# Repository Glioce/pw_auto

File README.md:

# pw_auto
PowherWheels modificado que se estaciona automáticamente.  

El cerebro del vehículo es una TIVA C EK-TM4C1294XL  
https://www.ti.com/tool/EK-TM4C1294XL  

> Tiva C Series  
> Connected LaunchPad  
> Booster Pack 2  
> TM4C1294  
> EK - TM4C1294XL  
> ARM Cortex M4F-Based  

## Ambientes de desarrollo
Se puede programar con las herramientas que proporciona Texas Instruments o con Energia IDE  
CCS IDE https://www.ti.com/tool/CCSTUDIO  
TivaWare https://www.ti.com/tool/SW-TM4C  
¿Editor online? https://dev.ti.com/  

Energia IDE se puede descargar sin registrarse y es como Arduino  
https://energia.nu/  
Tarjetas soportadas  
https://energia.nu/pinmaps/  

### Usando Energia
Descargar y abrir el IDE Energia. Instalar el paquete para programar Tiva C
en el menú Herramientas / Placas / Gestor de tarjetas, buscar TM, instalar.  

Conectar la tarjeta a la computadora usando el conector debug.
(parece que el otro conector es USB OTG)  

Guide to the TM4C129 Connected LaunchPad (EK-TM4C1294XL)  
https://energia.nu/pinmaps/ek-tm4c1294xl/  

Language reference (se parece a Arduino)  
https://energia.nu/reference/  

### Usando Code Composer Studio (CCS)
Iniciar el instalador y seleccionar el tipo de procesador de la tarjeta para instalar definiciones y compiladores.  

---

### Algoritmo
El vehículo se puede controlar de forma manual o funcionar en modo automático.
Cuando está en modo automático usa 4 sensores ultrasónicos. Dos sensores están instalados en el costado izquierdo del vehículo,
un sensor está instalado en la parte frontal y otro en la parte trasera.

Estado 0  
El vehículo avanza en línea recta. Hasta que los dos sensores laterales encuentran espacio suficiente para estacionarse.  
¿Necesita condiciones especiales para evitar errores?  
Los sensores pueden detectar suficiente espacio desde el inicio.  
Los sensores pueden detectar obstáculos desde el inicio (condición ideal).  
Un sensor detecta obstáculo y el otro ve un espacio libre. ¿Debe avanzar hacia adelante siempre?  
Al avanzar desde la condición ideal detectando obstáculos con los dos sensores laterales, ¿debe detectarse espacio con el sensor frontal primero?  
Lo más fácil es avanzar hasta que los dos sensores laterales detectan espacio.  

Estado 1  
Cuando los sensores laterales detectaron espacio. El vehículo sigue avanzando hasta que el sensor lateral frontal detecta obstáculo.  
Es importante notar que en los estados no se usan temporizadores,
solo se leen valores de los sensores para actuar. De esa forma la velocidad de desplazamiento se puede ajustar sin modificiar otras partes del programa.  

Estado 2  
La dirección gira a la izquierda y el vehículo comienza a avanzar en reversa.
El vehículo se introduce en el espacio disponible hasta que el sensor trasero detecta obstáculo.  
La distancia de detección de obstáculo debe ser un poco mayor a la distancia de estados anteriores.  

Estado 3  
La dirección gira a la derecha y el vehículo sigue avanzando en reversa.  
Con este movimiento el vehículo se va alineando al rectángulo disponible para estacionarse.  
Se detiene cuando detecta de nuevo un obstáculo con el sensor trasero.  

Estado 4  
Reposo. El vehículo ya está estacionado. En teoría debería quedar alineado y los sensores laterales deberían detectar un obstáculo cercano.  
Tal vez se puede mover un poco para que los sensores frontal y trasero detecten la misma distancia a sus respectivos obstáculos.  

Prevención de colisiones.  
Cada estado usa las lecturas de sensores específicos para determinar si debe cambiar al siguiente estado,
sin embargo, se usan los 4 sensores todo el tiempo. Si se detecta un objeto cercano en un momento inesperado, el vehículo se detiene.  

----
¿Ejemplo BLE?  
https://www.ti.com/tool/TIDM-TM4C129XBLE  

----
## Notas

Torque de wiper motor  
https://www.youtube.com/watch?v=hoxBkrD4xCo  

Ideas para wiper motor  
http://www.scary-terry.com/wipmtr/wipmtr2.htm  

L298 datasheet  
https://www.sparkfun.com/datasheets/Robotics/L298_H_Bridge.pdf  

IBT_2 tienada invento  
https://web.inventoteca.com/shop/product/puente-h-ibt-2-arduino-278?search=ibt  
http://www.hessmer.org/blog/2013/12/28/ibt-2-h-bridge-with-arduino/  

BTS7960  
https://www.handsontec.com/dataspecs/module/BTS7960%20Motor%20Driver.pdf  
https://articulo.mercadolibre.com.mx/MLM-613082284-modulo-puente-h-bts7960-43a-arduino-pic-_JM  

Puente H TIP41  
https://articulo.mercadolibre.com.mx/MLM-559425400-puente-h-4-amps-3-36-v-arduino-pic-robot-_JM  
https://www.youtube.com/watch?v=dnmWR5z8qPU  

Teoría Puente H con transistores de potencia  
http://tecnobotica.com/index.php/diplomados/tutoriales/41-puente-h-con-transistores  
https://www.diarioelectronicohoy.com/blog/el-puente-h-h-bridge  
http://salvador.maciashernandez.com/Proyectos/PuenteH/PuenteH.htm  
https://www.neoteo.com/puente-h-con-mosfet-para-motores-cc/  

Servos  
https://servodatabase.com/servo/towerpro/mg995  
https://servodatabase.com/servo/futaba/s3004  

### Varios videos

Ejemplo de carrito modificado. No tiene mucha info de la parte mecánica, pero explica el tipo de motores utilizados y las conexiones  
https://www.youtube.com/watch?v=AcVkwMPjTos  

https://www.youtube.com/watch?v=kzbhZqHqDM4  
También recomienda actuador lineal para la dirección  

https://www.youtube.com/watch?v=bRXtnwlUMdg  
Mejor detalle del actuador lineal  

https://www.youtube.com/watch?v=jNAeYGaALlQ  
Versión con servo. El carro es pequeño  

https://www.youtube.com/watch?v=kbLrQpJD--s  
Polea, alambre y motorreductor de la ventana de un Chevy Cavalier  
No menciona el sensor que utiliza para saber la posición del motor  
https://imgur.com/a/JXyOk  
Diagrama  

https://www.youtube.com/watch?v=n1nEr1FM19E  
Usar circuito de servo para controlar otro motorreductor  

https://www.youtube.com/watch?v=bURsvNdro4o  
Convertir motor de limpia parabrisas a servo  

https://www.youtube.com/watch?v=bi74u1eqCec  
Usa motor de regulador de ventana  

https://www.youtube.com/watch?v=spRwU4s4rTw  
Motor de limpia parabrisas convertido a servo  

https://www.youtube.com/watch?v=T5xMn2v7UGc  
Otra conversión de motor de limpia parabrisas a servo

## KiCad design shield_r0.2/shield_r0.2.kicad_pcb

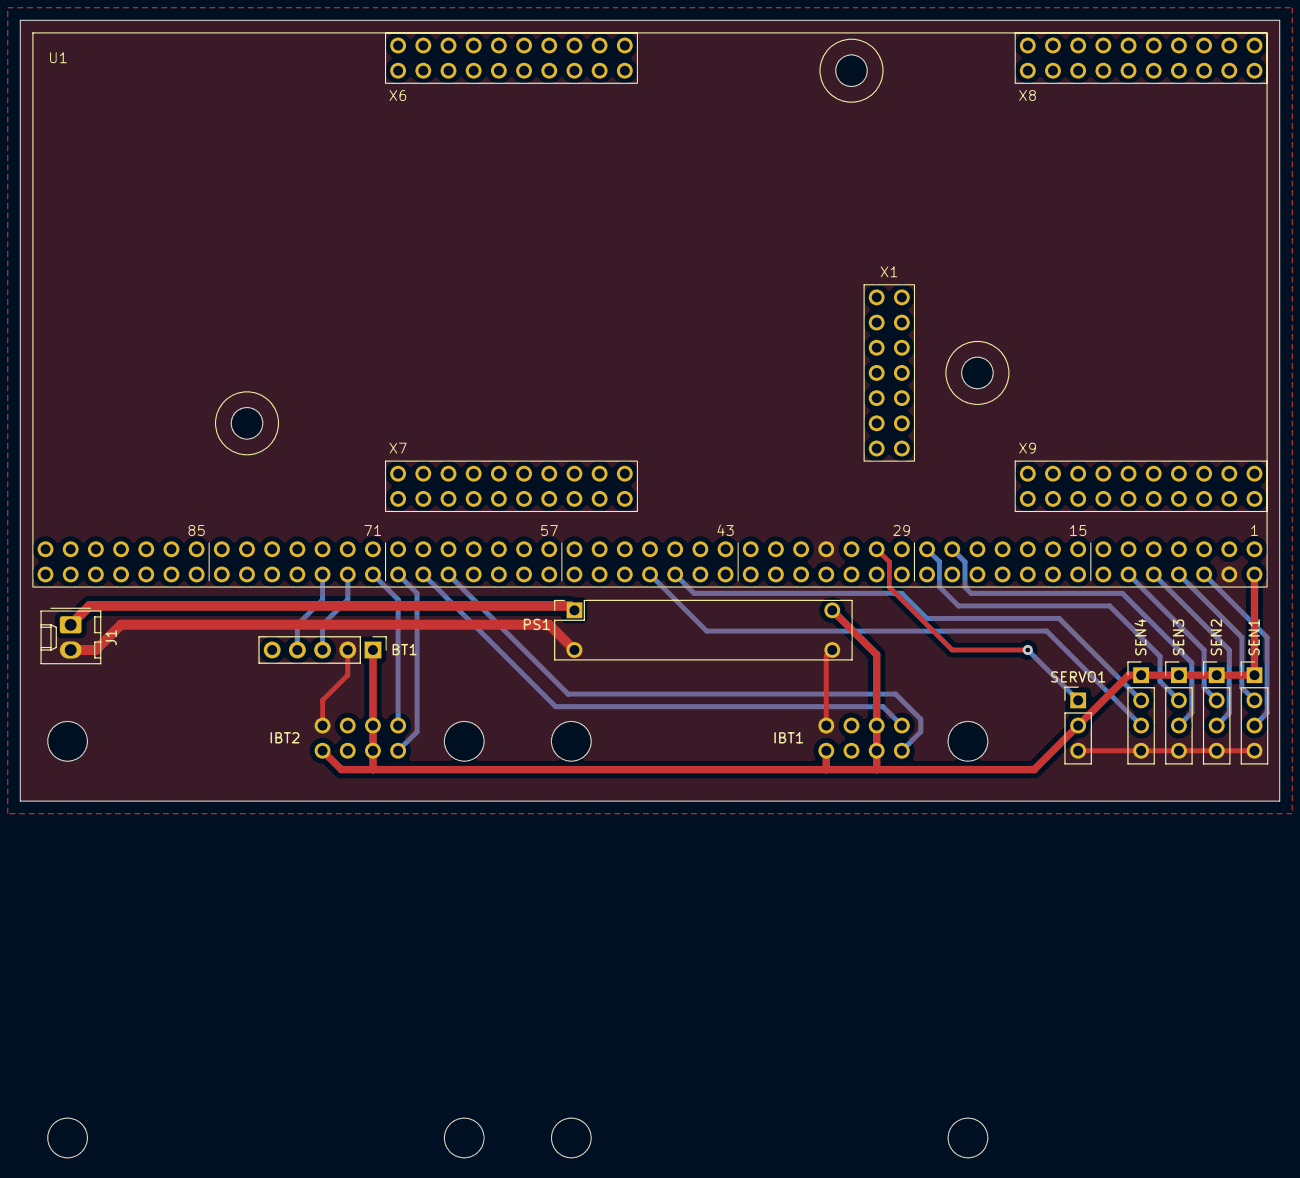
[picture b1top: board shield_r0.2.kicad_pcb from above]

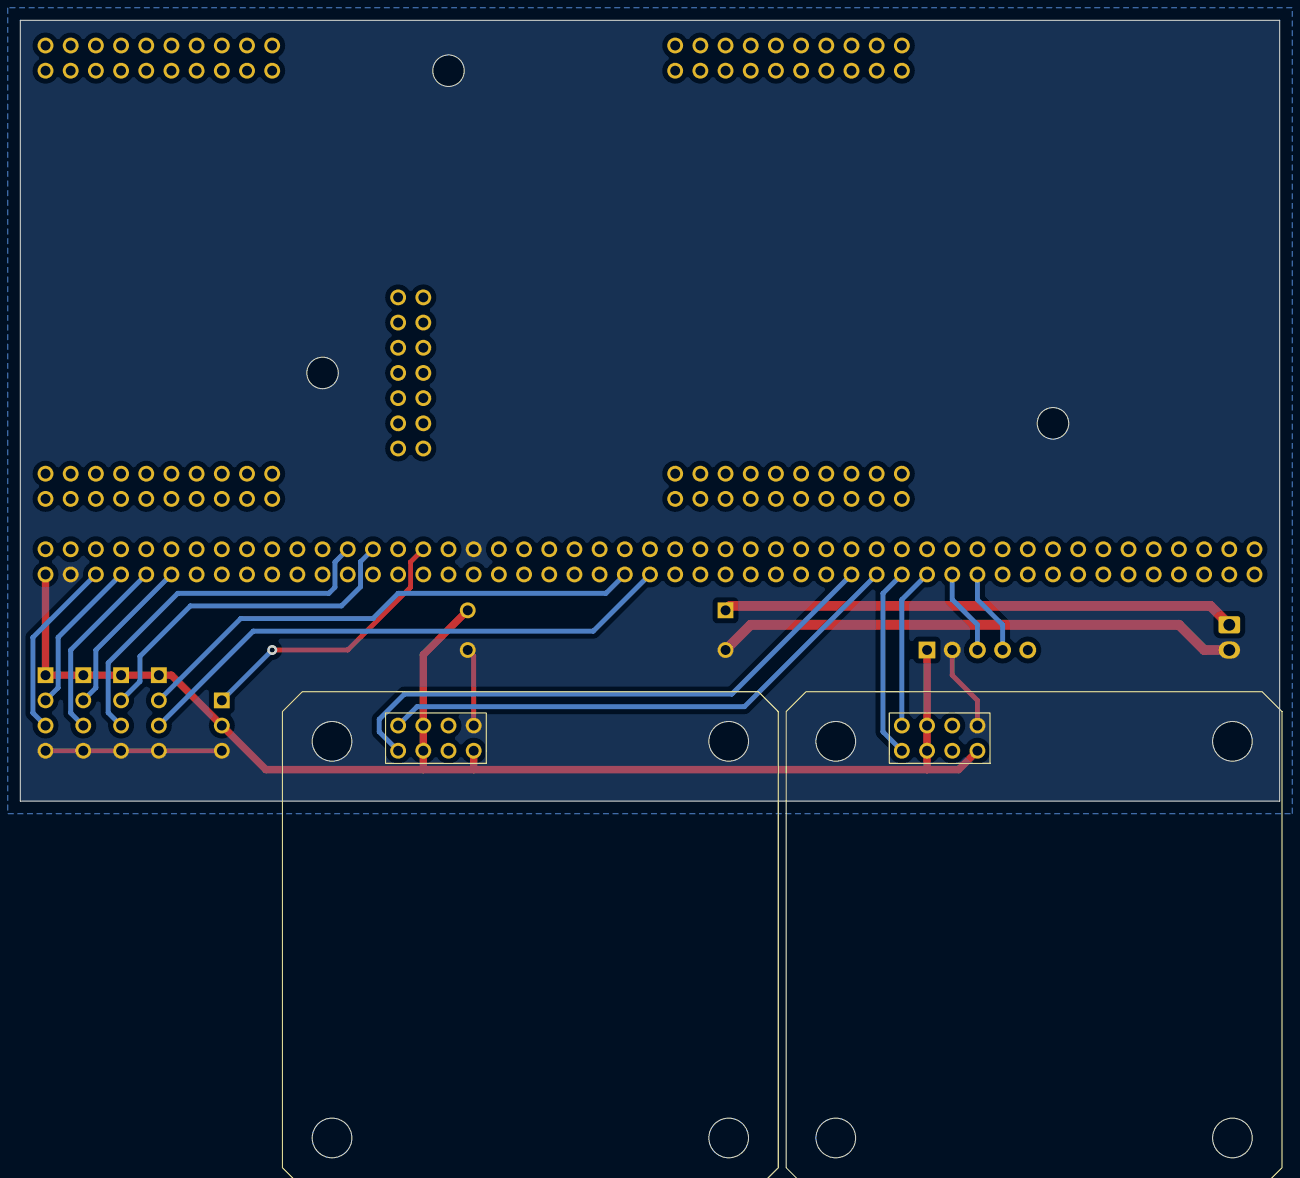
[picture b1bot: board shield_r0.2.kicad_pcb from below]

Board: 2 copper layers, 127.0 x 78.7 mm, 11 parts (2 on the bottom side), 18 nets.

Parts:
BT1: Conn_01x05; PinHeader_1x05_P2.54mm_Vertical
IBT1, IBT2: Conn_02x04_Odd_Even; IBT_2-01
J1: 12V; Molex_KK-254_AE-6410-02A_1x02_P2.54mm_Vertical
PS1: REGULADOR; PinHeader_2x02_P2.54mm_Vertical
SEN1, SEN2, SEN3, SEN4: Conn_01x04; PinHeader_1x04_P2.54mm_Vertical
SERVO1: Conn_01x03; PinHeader_1x03_P2.54mm_Vertical
U1: EK-TM4C1294XL; EK-TM4C1294XL-01

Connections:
+5V: BT1.1, IBT1.3, IBT1.4, IBT1.7, IBT2.3, IBT2.4, IBT2.7, PS1.3 (OUT+), SEN1.1, SEN2.1, SEN3.1, SEN4.1, SERVO1.2, U1.2 (5V)
+12V: J1.1, PS1.1 (IN+)
/ECHO1: SEN1.3, U1.6 (PA2)
/ECHO2: SEN2.3, U1.10 (PA4)
/ECHO3: SEN3.3, U1.25 (PA6)
/ECHO4: SEN4.3, U1.50 (PD0)
/LPWM1: IBT1.2, U1.68 (PF1)
/LPWM2: IBT2.2, U1.72 (PF3)
/RPWM1: IBT1.1, U1.66 (PF0)
/RPWM2: IBT2.1, U1.70 (PF2)
/RX0: BT1.3, U1.74 (PA0)
/SERVO1: SERVO1.1, U1.31 (PG0)
/TRIG1: SEN1.2, U1.8 (PA3)
/TRIG2: SEN2.2, U1.12 (PA5)
/TRIG3: SEN3.2, U1.27 (PA7)
/TRIG4: SEN4.2, U1.48 (PD1)
/TX0: BT1.4, U1.76 (PA1)
GND: BT1.2, IBT1.8, IBT2.8, J1.2, PS1.2 (IN-), PS1.4 (OUT-), SEN1.4, SEN2.4, SEN3.4, SEN4.4, SERVO1.3, U1.4 (GND), U1.35 (GND)

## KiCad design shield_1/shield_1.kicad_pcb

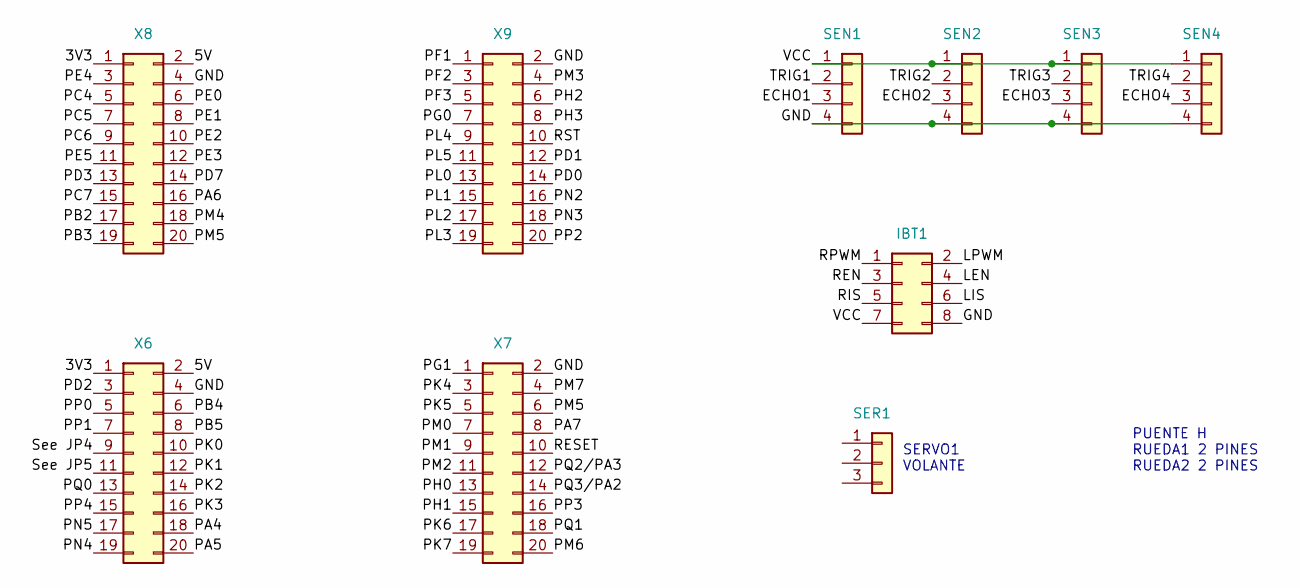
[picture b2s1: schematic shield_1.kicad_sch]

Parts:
IBT1: Conn_02x04_Odd_Even; PinHeader_2x04_P2.54mm_Vertical
SEN1, SEN2, SEN3, SEN4: Conn_01x04; PinHeader_1x04_P2.54mm_Vertical
SER1: Conn_01x03; PinHeader_1x03_P2.54mm_Vertical
X6: X6; PinHeader_2x10_P2.54mm_Vertical
X7: X7; PinHeader_2x10_P2.54mm_Vertical
X8: X8; PinHeader_2x10_P2.54mm_Vertical
X9: X9; PinHeader_2x10_P2.54mm_Vertical

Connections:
/3V3: X6.1, X8.1
/5V: X6.2, X8.2
/ECHO1: SEN1.3
/ECHO2: SEN2.3
/ECHO3: SEN3.3
/ECHO4: SEN4.3
/GND: IBT1.8, SEN1.4, SEN2.4, SEN3.4, SEN4.4, X6.4, X7.2, X8.4, X9.2
/LEN: IBT1.4
/LIS: IBT1.6
/LPWM: IBT1.2
/PA4: X6.18
/PA5: X6.20
/PA6: X8.16
/PA7: X7.8
/PB2: X8.17
/PB3: X8.19
/PB4: X6.6
/PB5: X6.8
/PC4: X8.5
/PC5: X8.7
/PC6: X8.9
/PC7: X8.15
/PD0: X9.14
/PD1: X9.12
/PD2: X6.3
/PD3: X8.13
/PD7: X8.14
/PE0: X8.6
/PE1: X8.8
/PE2: X8.10
/PE3: X8.12
/PE4: X8.3
/PE5: X8.11
/PF1: X9.1
/PF2: X9.3
/PF3: X9.5
/PG0: X9.7
/PG1: X7.1
/PH0: X7.13
/PH1: X7.15
/PH2: X9.6
/PH3: X9.8
/PK0: X6.10
/PK1: X6.12
/PK2: X6.14
/PK3: X6.16
/PK4: X7.3
/PK5: X7.5
/PK6: X7.17
/PK7: X7.19
/PL0: X9.13
/PL1: X9.15
/PL2: X9.17
/PL3: X9.19
/PL4: X9.9
/PL5: X9.11
/PM0: X7.7
/PM1: X7.9
/PM2: X7.11
/PM3: X9.4
/PM4: X8.18
/PM5: X7.6, X8.20
/PM6: X7.20
/PM7: X7.4
/PN2: X9.16
/PN3: X9.18
/PN4: X6.19
/PN5: X6.17
/PP0: X6.5
/PP1: X6.7
/PP2: X9.20
/PP3: X7.16
/PP4: X6.15
/PQ0: X6.13
/PQ1: X7.18
/PQ2/PA3: X7.12
/PQ3/PA2: X7.14
/REN: IBT1.3
/RESET: X7.10
/RIS: IBT1.5
/RPWM: IBT1.1
/RST: X9.10
/See JP4: X6.9
/See JP5: X6.11
/TRIG1: SEN1.2
/TRIG2: SEN2.2
/TRIG3: SEN3.2
/TRIG4: SEN4.2
/VCC: IBT1.7, SEN1.1, SEN2.1, SEN3.1, SEN4.1

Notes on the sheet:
SERVO1 VOLANTE
PUENTE H RUEDA1 2 PINES RUEDA2 2 PINES

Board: 2 copper layers, 10 parts (0 on the bottom side), 5 nets, no tracks yet.

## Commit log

2021-02-17 primeros enlaces
2021-03-15 Nota matrícula procesador
2021-03-16 Codigo base
2021-03-20 Descripción algoritmo
2022-12-26 crear proyecto shield1
2025-03-17 tamaño ajustado a 11cm x 11cm
2025-04-08 crear librerías ibt-2 y tiva-c, muestra shield
2025-04-10 conector bluetooth
2025-04-15 shield para fabricar
